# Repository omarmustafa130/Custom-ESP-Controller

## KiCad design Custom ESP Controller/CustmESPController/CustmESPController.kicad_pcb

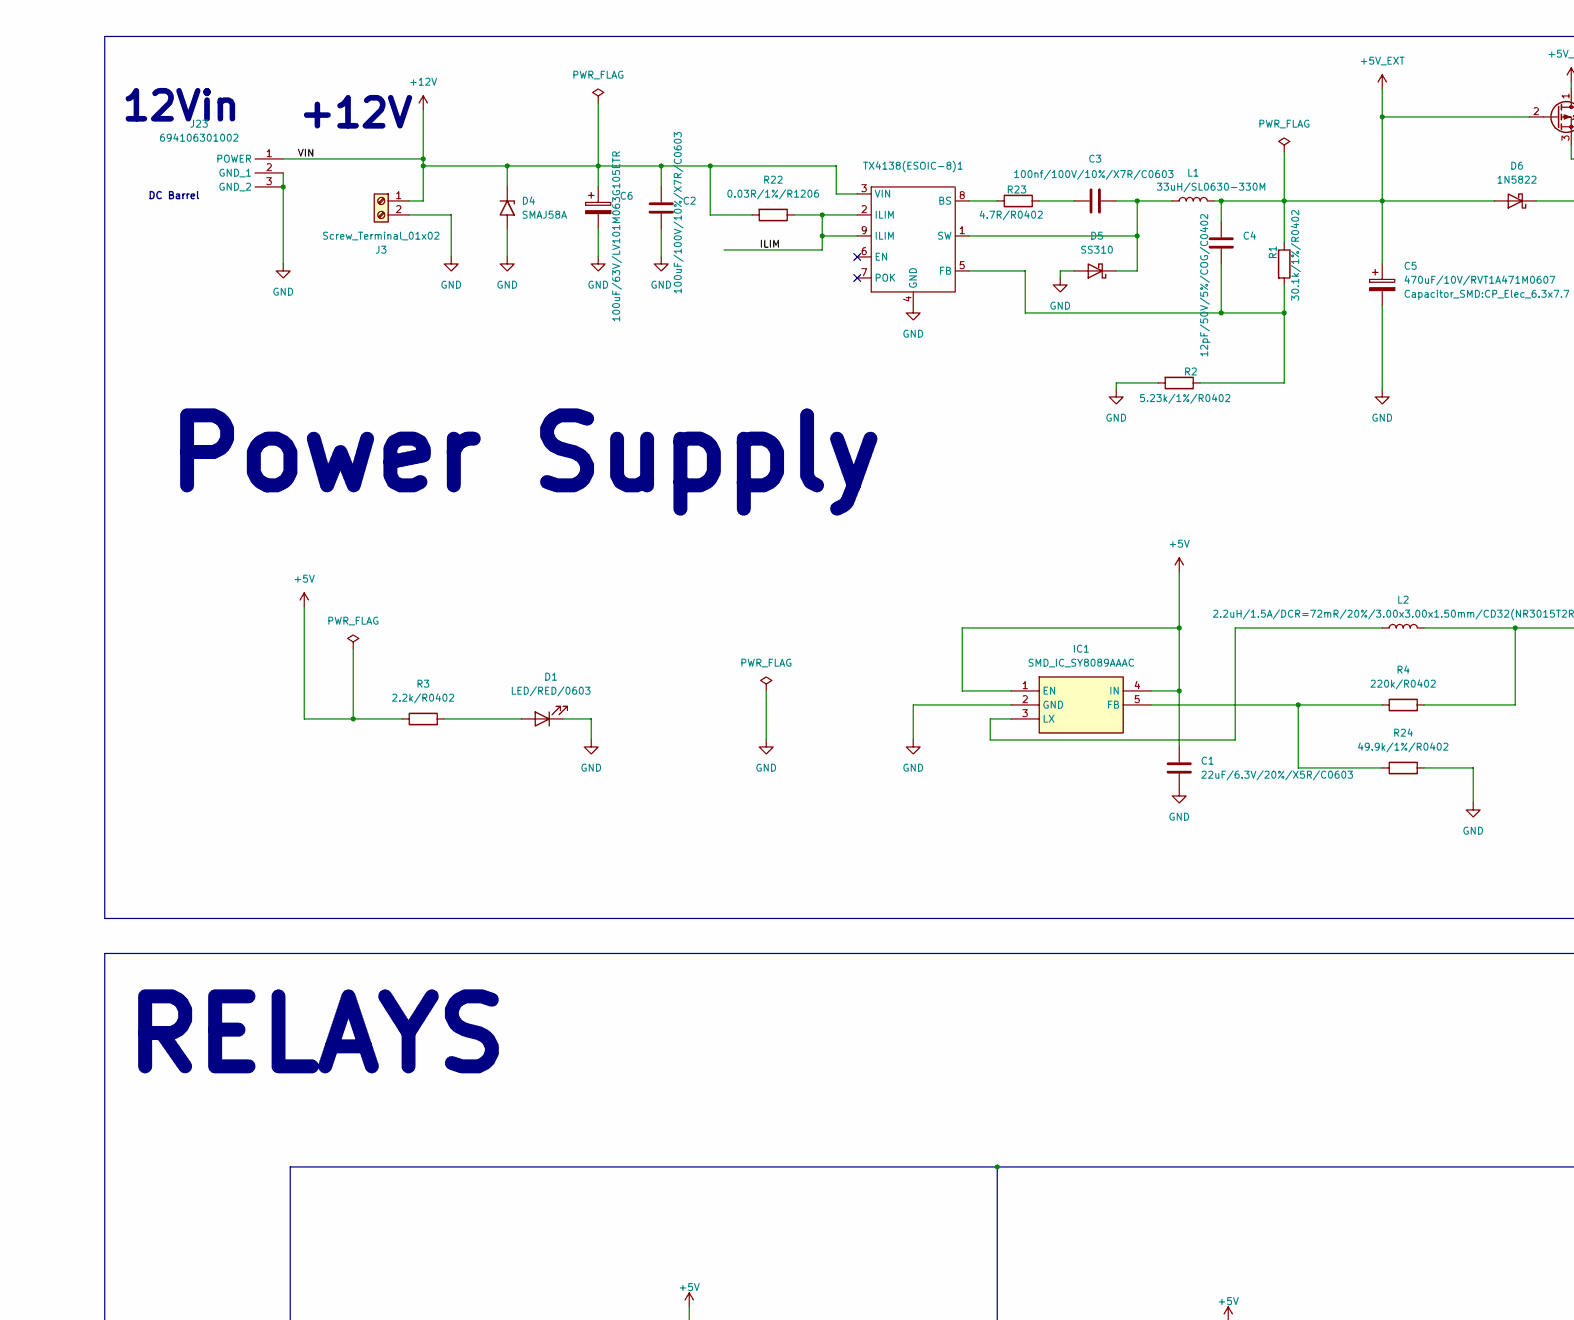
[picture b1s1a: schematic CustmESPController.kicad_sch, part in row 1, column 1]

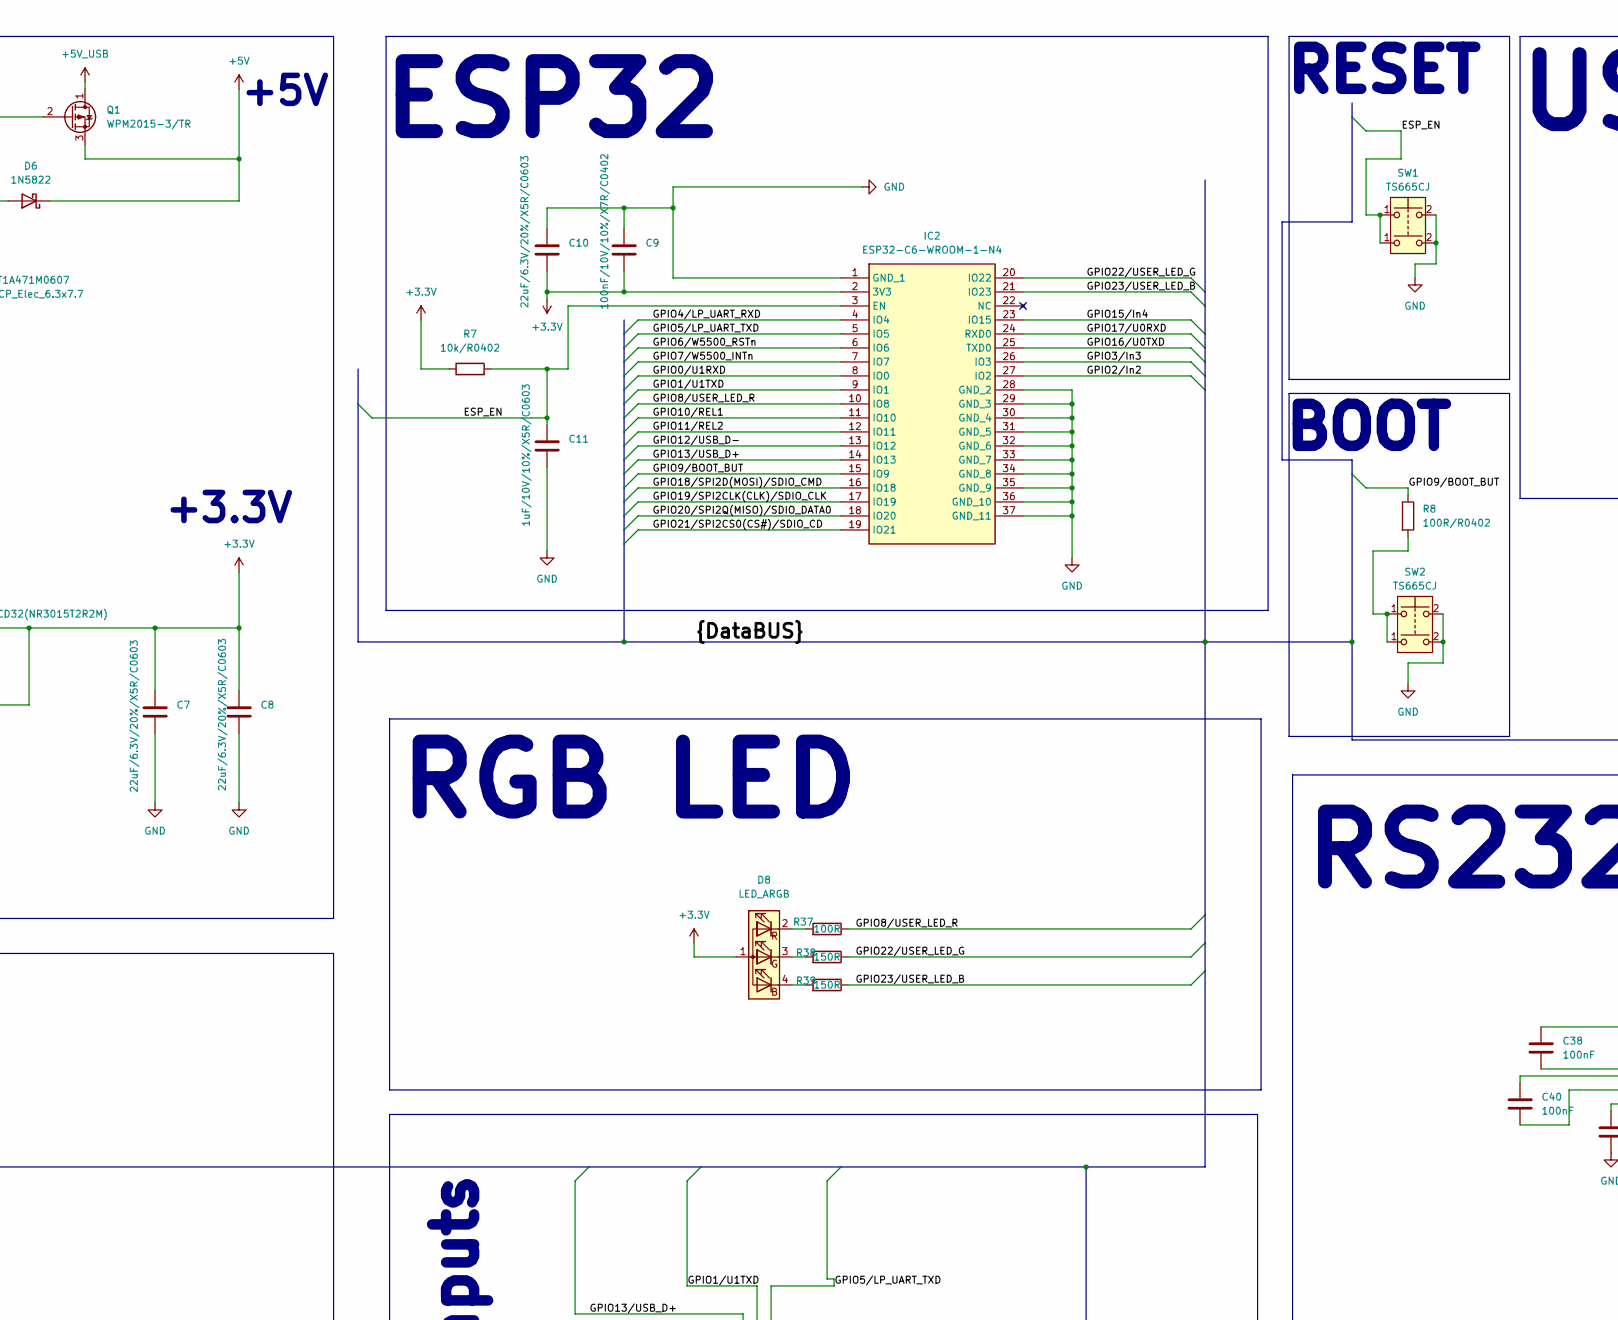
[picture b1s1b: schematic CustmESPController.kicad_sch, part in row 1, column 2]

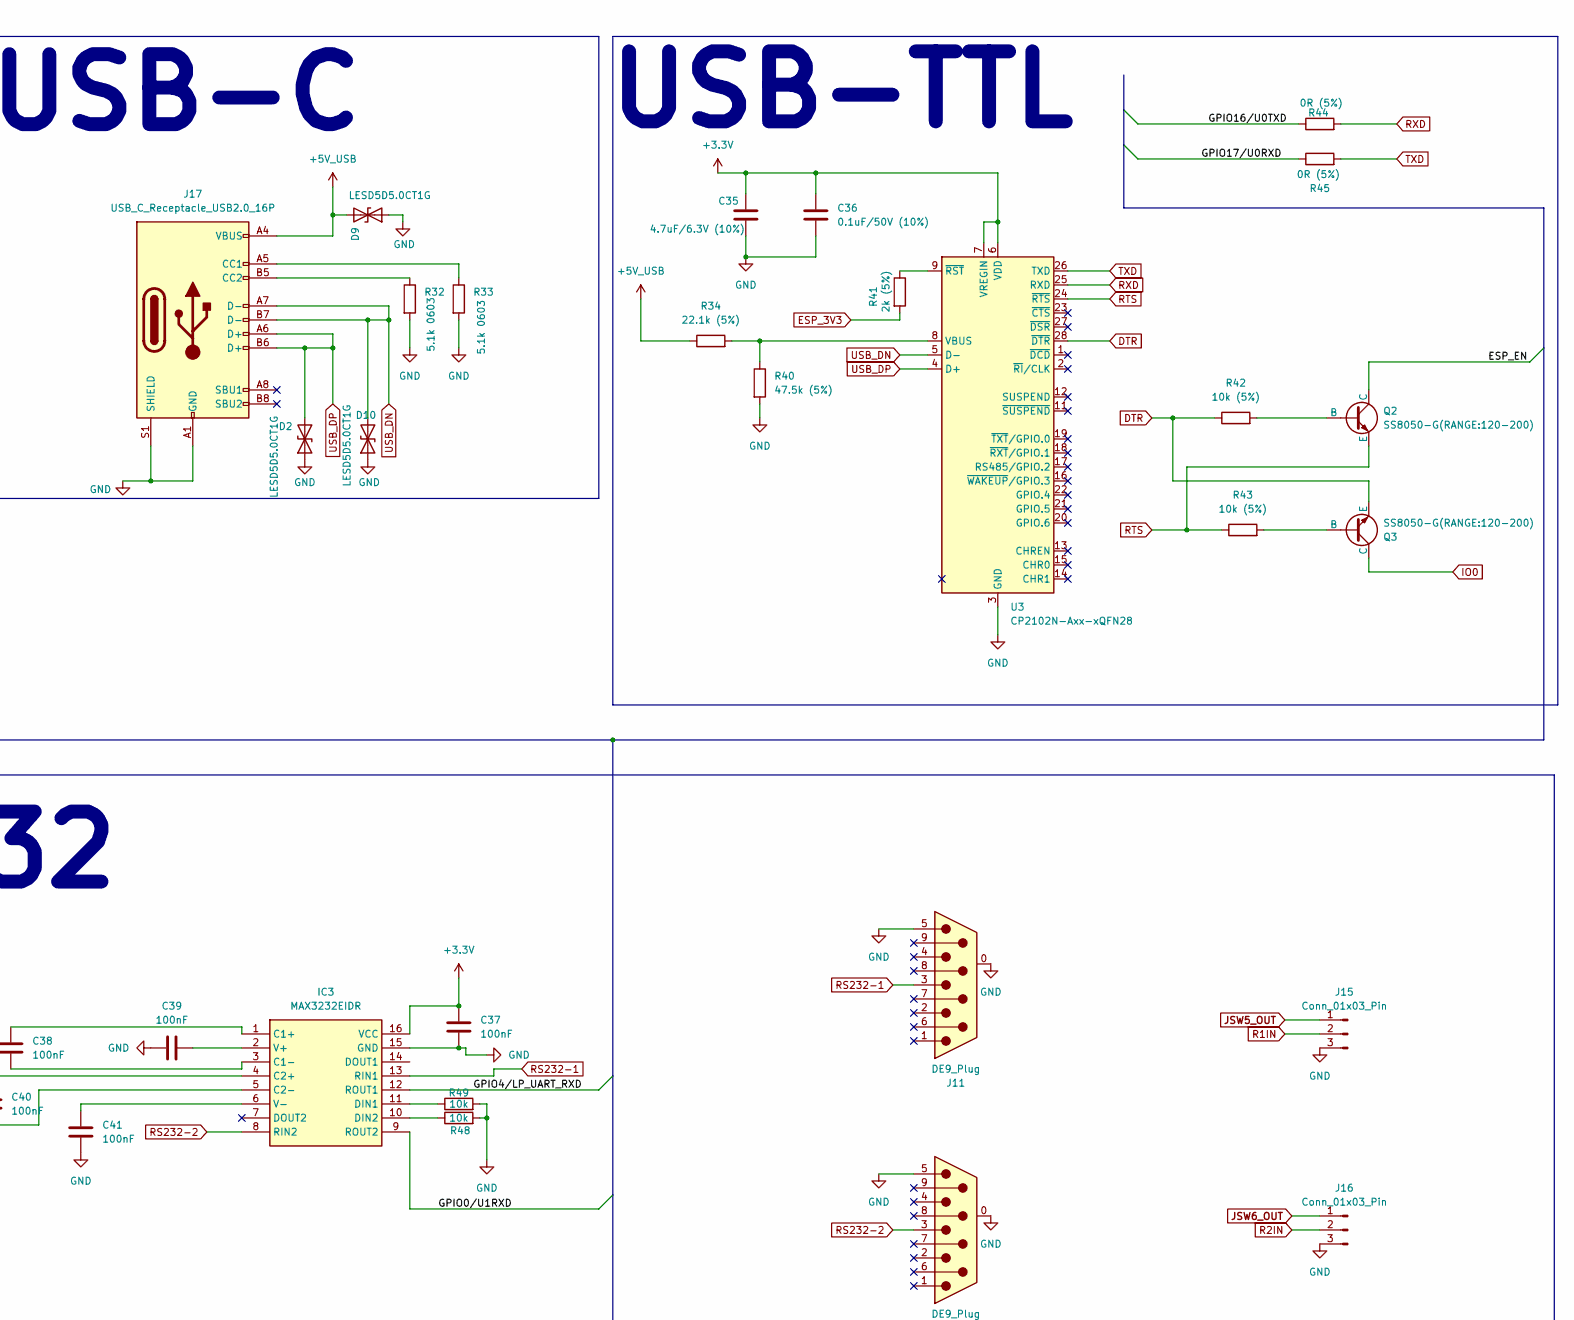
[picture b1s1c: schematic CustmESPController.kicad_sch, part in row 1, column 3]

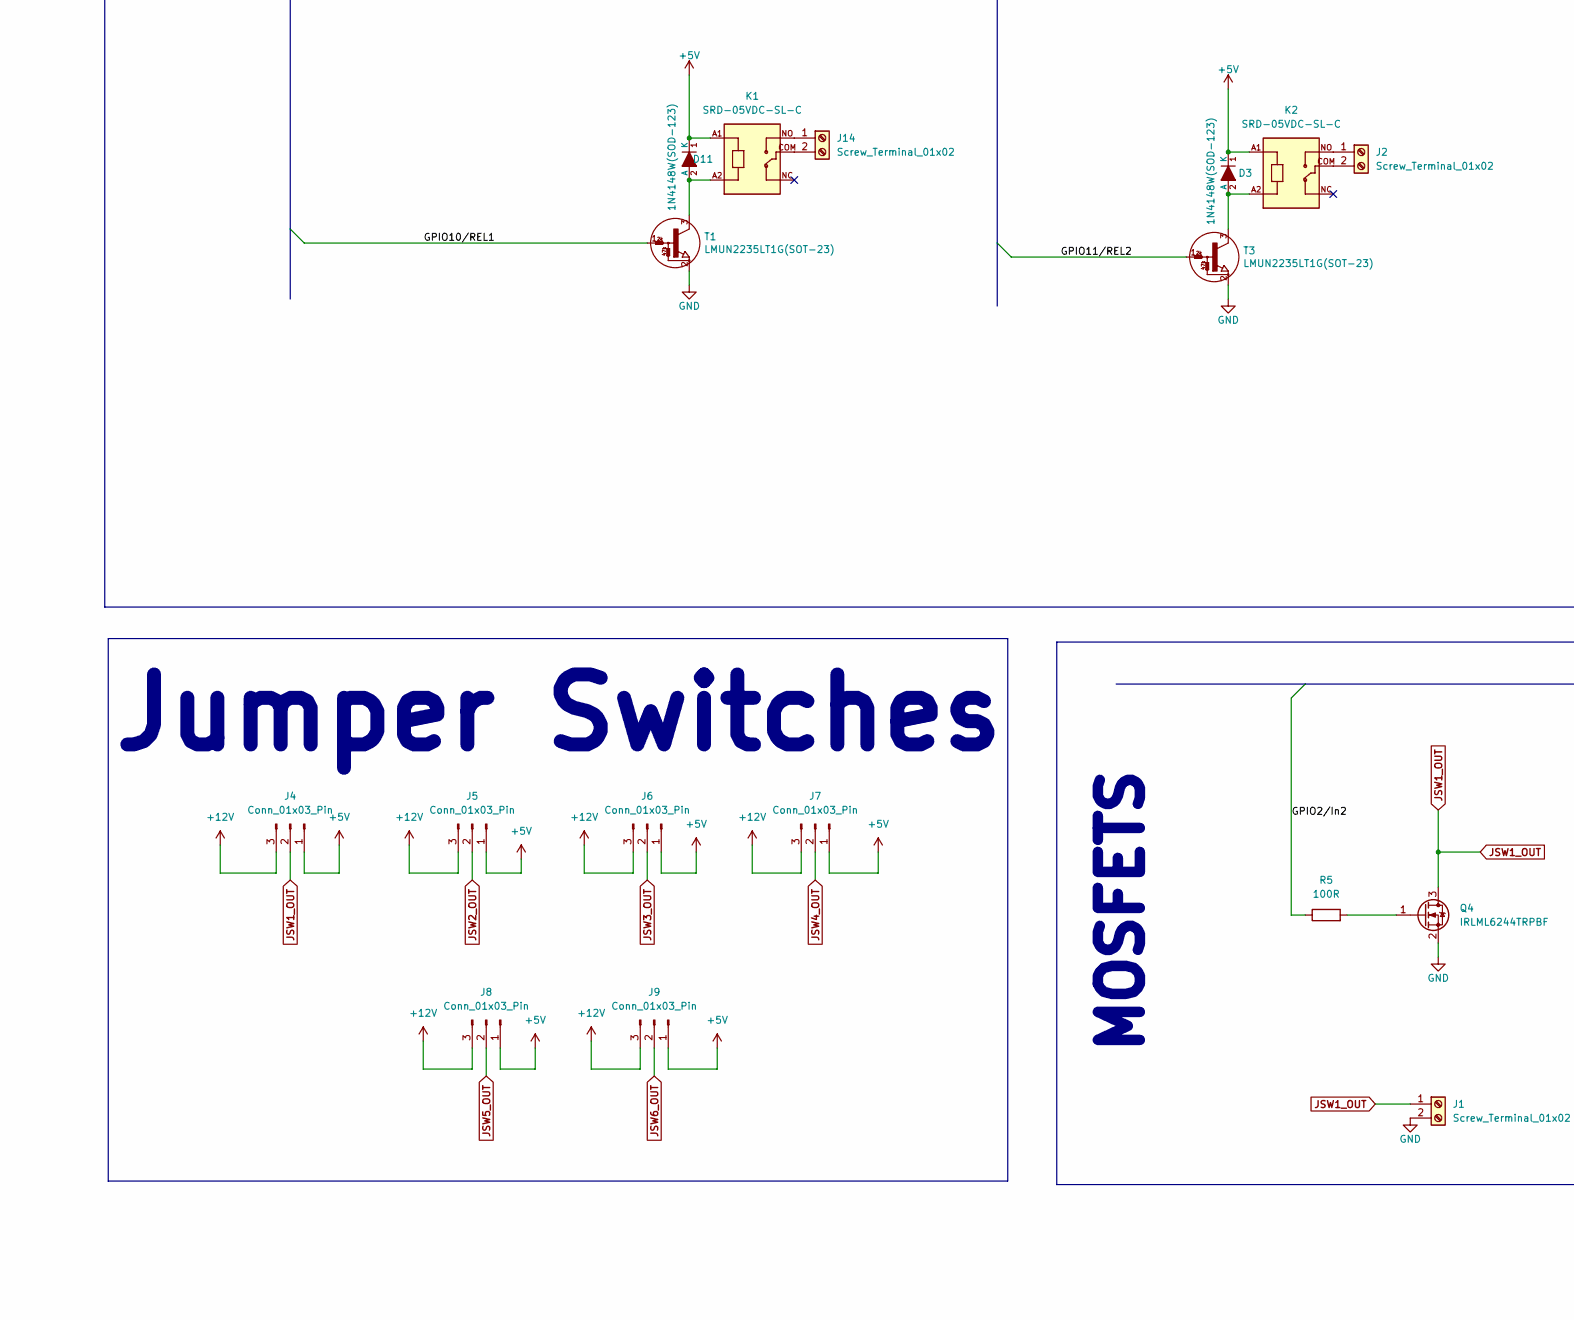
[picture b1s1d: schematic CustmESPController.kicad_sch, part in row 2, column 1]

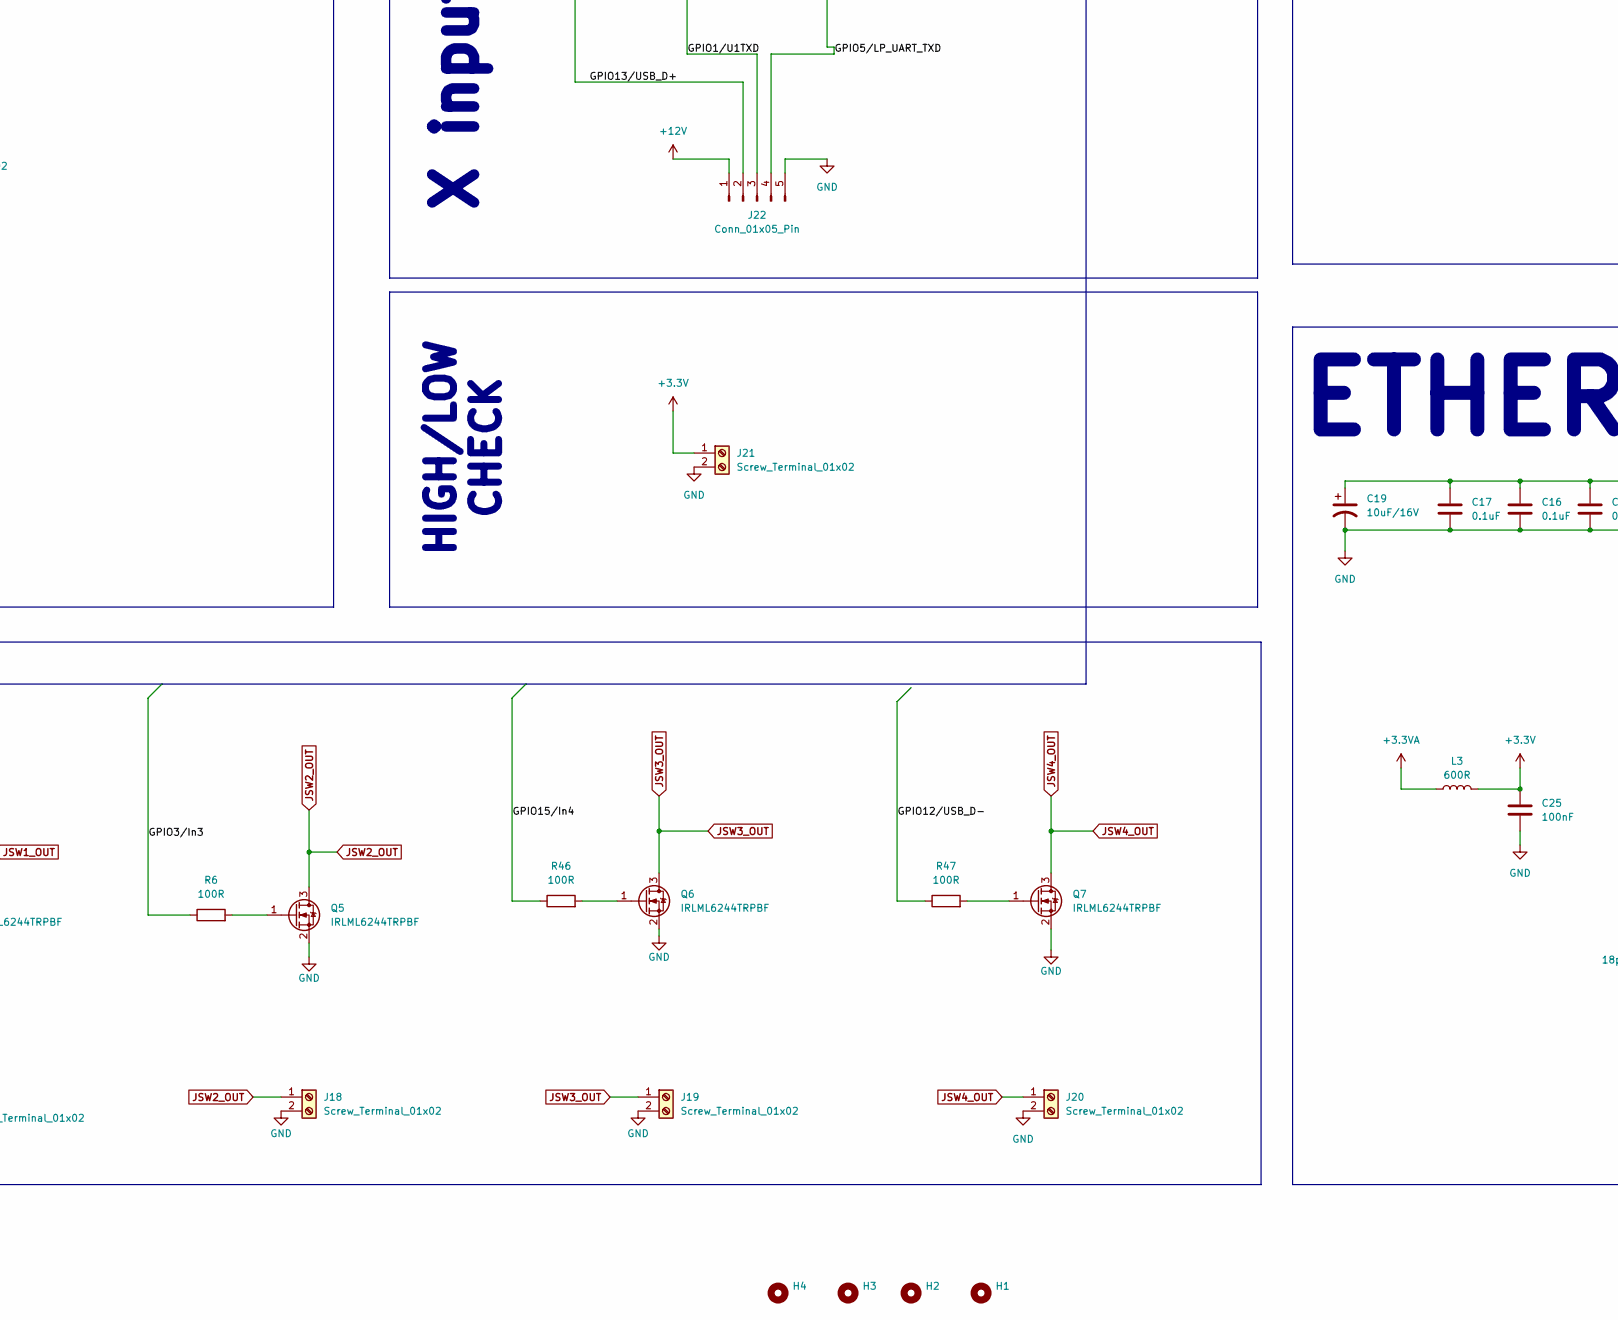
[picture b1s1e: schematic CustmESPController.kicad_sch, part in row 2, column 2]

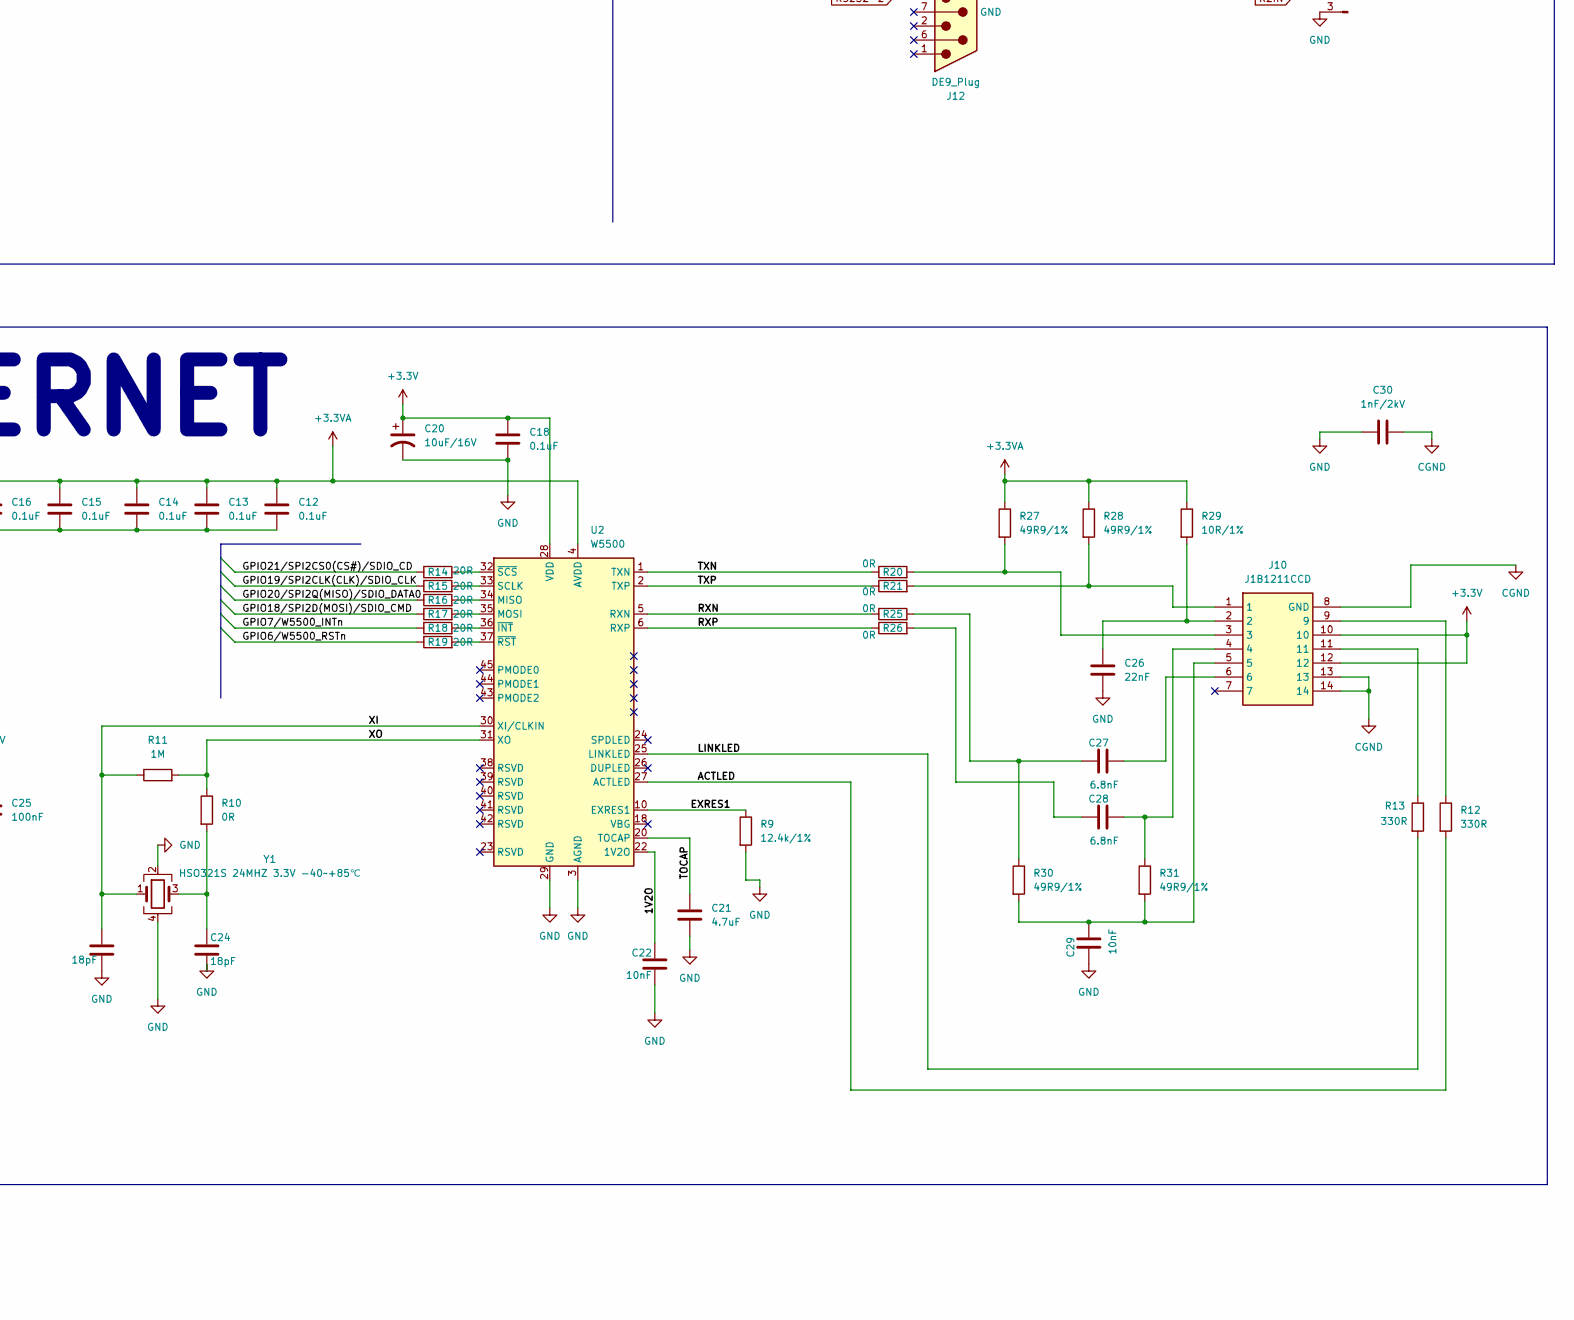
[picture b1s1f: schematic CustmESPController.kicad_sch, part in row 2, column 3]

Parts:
C1, C7, C8, C10: 22uF/6.3V/20%/X5R/C0603; C_0603_1608Metric
C2: 100uF/100V/10%/X7R/C0603; C_0603_1608Metric
C3: 100nf/100V/10%/X7R/C0603; C_0603_1608Metric
C4: 12pF/50V/5%/COG/C0402; C_0402_1005Metric
C5: 470uF/10V/RVT1A471M0607; CP_Elec_6.3x7.7
C6: 100uF/63V/LV101M063G105ETR; CP_Elec_10x10.5
C9: 100nF/10V/10%/X7R/C0402; C_0402_1005Metric
C11: 1uF/10V/10%/X5R/C0603; C_0603_1608Metric
C12, C13, C14, C15, C16, C17, C18: 0.1uF; C_0402_1005Metric
C19, C20: 10uF/16V; C_0603_1608Metric
C21: 4.7uF; C_0402_1005Metric
C22, C29: 10nF; C_0402_1005Metric
C23, C24: 18pF; C_0402_1005Metric
C25: 100nF; C_0402_1005Metric
C26: 22nF; C_0402_1005Metric
C27, C28: 6.8nF; C_0402_1005Metric
C30: 1nF/2kV; C_0402_1005Metric
C35: 4.7uF/6.3V (10%); C_0603_1608Metric
C36: 0.1uF/50V (10%); C_0603_1608Metric
C37, C38, C39, C40, C41: 100nF; C_0603_1608Metric
D1: LED/RED/0603; LED_0603_1608Metric
D2, D9, D10: LESD5D5.0CT1G; LESD5D5.0CT1G_DTVS
D3, D11: 1N4148W(SOD-123); 1N4148W_SODFL3816X120N
D4: SMAJ58A; SMAJ58A_DIOM5026X229N
D5: SS310; DIO_SS310
D6: 1N5822; 1N5822_DIOAD3070W130L950D530
D8: LED_ARGB; LED_D5.0mm-4_RGB
H1, H2, H3, H4: MountingHole_2.2mm_M2
IC1: SMD_IC_SY8089AAAC; SY80B9AAAC_SOT95P285X140-5N; Mouser Part Number 909-SMDICSY8089AAAC
IC2: ESP32-C6-WROOM-1-N4; ESP32C6WROOM1N4; Mouser Part Number 356-ESP32C6WROOM1N4
IC3: MAX3232EIDR; MAX3232EIDR_SOIC127P600X175-16N; Mouser Part Number 595-MAX3232EIDR
J1, J2, J3, J14, J18, J19, J20, J21: Screw_Terminal_01x02; TerminalBlock_Altech_AK300-2_P5.00mm
J4, J5, J6, J7, J8, J9: Conn_01x03_Pin; PinHeader_1x03_P2.54mm_Vertical
J10: J1B1211CCD; Mouser Part Number 950-J1B1211CCD
J11, J12: DE9_Plug; DSUB-9_Female_Vertical_P2.77x2.84mm_MountingHoles
J15, J16: Conn_01x03_Pin; JST_EH_B3B-EH-A_1x03_P2.50mm_Vertical
J17: USB_C_Receptacle_USB2.0_16P; USB_C_Receptacle_HRO_TYPE-C-31-M-12
J22: Conn_01x05_Pin; JST_EH_B5B-EH-A_1x05_P2.50mm_Vertical
J23: 694106301002; 694106301002_1; Mouser Part Number 710-694106301002
K1, K2: SRD-05VDC-SL-C; RELAY_SRD-05VDC-SL-C
L1: 33uH/SL0630-330M; SL0630-330M
L2: 2.2uH/1.5A/DCR=72mR/20%/3.00x3.00x1.50mm/CD32(NR3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; IND_NR3015T2R2M
L3: 600R; L_0603_1608Metric
Q1: WPM2015-3/TR; WPM2015-3TR_SOT95P240X130-3N
Q2, Q3: SS8050-G(RANGE:120-200); SS8050_SOT95P240X115-3N
Q4, Q5, Q6, Q7: IRLML6244TRPBF; IRLML6244TRPBF_SOT95P237X112-3N
R1: 30.1k/1%/R0402; R_0402_1005Metric
R2: 5.23k/1%/R0402; R_0402_1005Metric
R3: 2.2k/R0402; R_0402_1005Metric
R4: 220k/R0402; R_0402_1005Metric
R5, R6, R46, R47: 100R; R_0402_1005Metric
R7: 10k/R0402; R_0402_1005Metric
R8: 100R/R0402; R_0402_1005Metric
R9: 12.4k/1%; R_0402_1005Metric
R10, R20, R21, R25, R26: 0R; R_0402_1005Metric
R11: 1M; R_0402_1005Metric
R12, R13: 330R; R_0402_1005Metric
R14, R15, R16, R17, R18, R19: 20R; R_0402_1005Metric
R22: 0.03R/1%/R1206; R_1206_3216Metric
R23: 4.7R/R0402; R_0402_1005Metric
R24: 49.9k/1%/R0402; R_0402_1005Metric
R27, R28, R30, R31: 49R9/1%; R_0402_1005Metric
R29: 10R/1%; R_0402_1005Metric
R32, R33: 5.1k 0603; R_0603_1608Metric
R34: 22.1k (5%); R_0603_1608Metric
R37: 100R; R_0603_1608Metric
R38, R39: 150R; R_0603_1608Metric
R40: 47.5k (5%); R_0603_1608Metric
R41: 2k (5%); R_0603_1608Metric
R42, R43: 10k (5%); R_0603_1608Metric
R44, R45: 0R (5%); R_0603_1608Metric
R48, R49: 10k; R_0402_1005Metric
SW1, SW2: TS665CJ; SW_PUSH_6mm
T1, T3: LMUN2235LT1G(SOT-23); LMUN2235LT1G
TX4138(ESOIC-8)1: TX4138_SOIC127P600X165-9N
U2: W5500; W5500_QFP50P900X900X160-48N
U3: CP2102N-Axx-xQFN28; CP2102N_QFN50P500X500X80-29N-D
Y1: HSO321S 24MHZ 3.3V -40~+85℃; HSO321S

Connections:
+3.3V: C7.1, C8.1, C9.2, C10.2, C18.1, C20.1, C25.1, C35.2, C36.2, C37.1, D8.1 (A), IC2.2 (3V3), IC3.16 (VCC), J10.10, J10.12, J21.1, L2.2, L3.2, R4.2, R7.1, U2.28 (VDD), U3.6 (VDD), U3.7 (VREGIN)
+3.3VA: C12.1, C13.1, C14.1, C15.1, C16.1, C17.1, C19.1, L3.1, R27.1, R28.1, R29.1, U2.4 (AVDD), U2.8 (AVDD), U2.11 (AVDD), U2.15 (AVDD), U2.17 (AVDD), U2.21 (AVDD)
+5V: C1.1, D3.1 (K), D6.1 (K), D11.1 (K), IC1.1 (EN), IC1.4 (IN), J4.1, J5.1, J6.1, J7.1, J8.1, J9.1, K1.A1, K2.A1, Q1.3 (S), R3.1
+5V_EXT: C4.1, C5.1, D6.2 (A), L1.2, Q1.2 (G), R1.1
+5V_USB: D9.2 (A2), J17.A4 (VBUS), J17.A9 (VBUS), J17.B4 (VBUS), J17.B9 (VBUS), Q1.1 (D), R34.1
+12V: C2.1, C6.1, D4.1 (A1), J3.1, J4.3, J5.3, J6.3, J7.3, J8.3, J9.3, J22.1, J23.1 (POWER), R22.2, TX4138(ESOIC-8)1.3 (VIN); also elsewhere on the board
/1V2O: C22.1, U2.22 (1V2O)
/ACTLED: R12.2, U2.27 (ACTLED)
/ESP_EN: C11.1, IC2.3 (EN), Q2.1 (C), R7.2, SW1.1
/EXRES1: R9.1, U2.10 (EXRES1)
/GPIO0/U1RXD: IC2.8 (IO0), IC3.9 (ROUT2)
/GPIO1/U1TXD: IC2.9 (IO1), J22.3
/GPIO2/In2: IC2.27 (IO2), R5.1
/GPIO3/In3: IC2.26 (IO3), R6.1
/GPIO4/LP_UART_RXD: IC2.4 (IO4), IC3.12 (ROUT1)
/GPIO5/LP_UART_TXD: IC2.5 (IO5), J22.4
/GPIO6/W5500_RSTn: IC2.6 (IO6), R19.1
/GPIO7/W5500_INTn: IC2.7 (IO7), R18.1
/GPIO8/USER_LED_R: IC2.10 (IO8), R37.1
/GPIO9/BOOT_BUT: IC2.15 (IO9), R8.1
/GPIO10/REL1: IC2.11 (IO10), T1.1 (B)
/GPIO11/REL2: IC2.12 (IO11), T3.1 (B)
/GPIO12/USB_D-: IC2.13 (IO12), R47.1
/GPIO13/USB_D+: IC2.14 (IO13), J22.2
/GPIO15/In4: IC2.23 (IO15), R46.1
/GPIO16/U0TXD: IC2.25 (TXD0), R44.1
/GPIO17/U0RXD: IC2.24 (RXD0), R45.1
/GPIO18/SPI2D(MOSI)/SDIO_CMD: IC2.16 (IO18), R17.1
/GPIO19/SPI2CLK(CLK)/SDIO_CLK: IC2.17 (IO19), R15.1
/GPIO20/SPI2Q(MISO)/SDIO_DATA0: IC2.18 (IO20), R16.1
/GPIO21/SPI2CS0(CS#)/SDIO_CD: IC2.19 (IO21), R14.1
/GPIO22/USER_LED_G: IC2.20 (IO22), R38.1
/GPIO23/USER_LED_B: IC2.21 (IO23), R39.1
/ILIM: R22.1, TX4138(ESOIC-8)1.2 (ILIM), TX4138(ESOIC-8)1.9 (ILIM); also elsewhere on the board
/LINKLED: R13.2, U2.25 (LINKLED)
/RXN: R25.1, U2.5 (RXN)
/RXP: R26.1, U2.6 (RXP)
/TOCAP: C21.1, U2.20 (TOCAP)
/TXN: R20.1, U2.1 (TXN)
/TXP: R21.1, U2.2 (TXP)
/XI: C23.1, R11.1, U2.30 (XI/CLKIN), Y1.1
/XO: R10.1, R11.2, U2.31 (XO)
CGND: C30.2, J10.8 (GND), J10.13, J10.14
DTR: Q3.3 (E), R42.1, U3.28 (~DTR)
ESP_3V3: R41.2
GND: C1.2, C2.2, C5.2, C6.2, C7.2, C8.2, C9.1, C10.1, C11.2, C12.2, C13.2, C14.2, C15.2, C16.2, C17.2, C18.2, C19.2, C20.2, C21.2, C22.2, C23.2, C24.2, C25.2, C26.2, C29.1, C30.1, C35.1, C36.1, C37.2, C39.1, C41.2, D1.1 (K), D2.1 (A1), D4.2 (A2), D5.2 (A), D9.1 (A1), D10.1 (A1), IC1.2 (GND), IC2.1 (GND_1), IC2.28 (GND_2), IC2.29 (GND_3), IC2.30 (GND_4), IC2.31 (GND_5), IC2.32 (GND_6), IC2.33 (GND_7), IC2.34 (GND_8), IC2.35 (GND_9), IC2.36 (GND_10), IC2.37 (GND_11), IC3.15 (GND), J1.2, J3.2, J11.0 (GND), J11.5, J12.0 (GND), J12.5, J15.3, J16.3, J17.A1 (GND), J17.A12 (GND), J17.B1 (GND), J17.B12 (GND), J17.S1 (SHIELD), J18.2, J19.2, J20.2, J21.2, J22.5, J23.2 (GND_1), J23.3 (GND_2), Q4.2 (S), Q5.2 (S), Q6.2 (S), Q7.2 (S), R2.2, R9.2, R24.2, R32.2, R33.2, R40.2, R48.2, R49.2, SW1.2, SW2.2, T1.2 (E), T3.2 (E), TX4138(ESOIC-8)1.4 (GND), U2.3 (AGND), U2.9 (AGND), U2.14 (AGND), U2.16 (AGND), U2.19 (AGND), U2.29 (GND), U2.48 (AGND), U3.3 (GND), U3.29 (GND), Y1.2, Y1.4; also elsewhere on the board
IO0: Q3.1 (C)
JSW1_OUT: J1.1, J4.2, Q4.3 (D)
JSW2_OUT: J5.2, J18.1, Q5.3 (D)
JSW3_OUT: J6.2, J19.1, Q6.3 (D)
JSW4_OUT: J7.2, J20.1, Q7.3 (D)
JSW5_OUT: J8.2, J15.1
JSW6_OUT: J9.2, J16.1
unnamed: C3.1, R23.2
unnamed: C24.1, R10.2, Y1.3
unnamed: C26.1, J10.2, R29.2
unnamed: C27.1, R25.2, R30.1
unnamed: C27.2, J10.6
unnamed: C28.1, R26.2
unnamed: C28.2, J10.4, R31.1
unnamed: C29.2, J10.5, R30.2, R31.2
unnamed: D1.2 (A), R3.2
unnamed: D3.2 (A), K2.A2, T3.3 (C)
unnamed 63: C3.2, D5.1 (K), L1.1, TX4138(ESOIC-8)1.1 (SW); also elsewhere on the board
unnamed: D8.4 (BK), R39.2
unnamed: D8.3 (GK), R38.2
unnamed: D8.2 (RK), R37.2
unnamed: D11.2 (A), K1.A2, T1.3 (C)
unnamed: IC1.5 (FB), R4.1, R24.1
unnamed: IC1.3 (LX), L2.1
unnamed: C38.1, IC3.1 (C1+)
unnamed: C38.2, IC3.3 (C1-)
unnamed: C40.1, IC3.4 (C2+)
unnamed: C40.2, IC3.5 (C2-)
unnamed: IC3.11 (DIN1), R49.1
unnamed: IC3.10 (DIN2), R48.1
unnamed: C39.2, IC3.2 (V+)
unnamed: C41.1, IC3.6 (V-)
unnamed: J2.1, K2.NO
unnamed: J2.2, K2.COM
unnamed: J10.1, R21.2, R28.2
unnamed: J10.3, R20.2, R27.2
unnamed: J10.9, R12.1
unnamed: J10.11, R13.1
unnamed: J14.1, K1.NO
unnamed: J14.2, K1.COM
unnamed: J17.A5 (CC1), R33.1
unnamed: J17.B5 (CC2), R32.1
unnamed: Q2.2 (B), R42.2
unnamed: Q3.2 (B), R43.2
unnamed: Q4.1 (G), R5.2
unnamed: Q5.1 (G), R6.2
unnamed: Q6.1 (G), R46.2
unnamed: Q7.1 (G), R47.2
unnamed: R8.2, SW2.1
unnamed 95: R23.1, TX4138(ESOIC-8)1.8 (BS); also elsewhere on the board
unnamed 96: C4.2, R1.2, R2.1, TX4138(ESOIC-8)1.5 (FB); also elsewhere on the board
unnamed: R16.2, U2.34 (MISO)
unnamed: R17.2, U2.35 (MOSI)
unnamed: R15.2, U2.33 (SCLK)
unnamed: R18.2, U2.36 (~INT)
unnamed: R19.2, U2.37 (~RST)
unnamed: R14.2, U2.32 (~SCS)
unnamed: R34.2, R40.1, U3.8 (VBUS)
unnamed: R41.1, U3.9 (~RST)
R1IN: J15.2
R2IN: J16.2
RS232-1: IC3.13 (RIN1), J11.3
RS232-2: IC3.8 (RIN2), J12.3
RTS: Q2.3 (E), R43.1, U3.24 (~RTS)
RXD: R44.2, U3.25 (RXD)
TXD: R45.2, U3.26 (TXD)
USB_DN: D10.2 (A2), J17.A7 (D-), J17.B7 (D-), U3.5 (D-)
USB_DP: D2.2 (A2), J17.A6 (D+), J17.B6 (D+), U3.4 (D+)

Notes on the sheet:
BOOT
12Vin
USB-C
ETHERNET
+5V
Jumper Switches
HIGH/LOW CHECK
RESET
X inputs
USB-TTL
Power Supply
DC Barrel
RELAYS
+3.3V
MOSFETS
RS232
+12V
RGB LED
ESP32

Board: 2 copper layers, 143 parts (0 on the bottom side), 110 nets, no tracks yet.

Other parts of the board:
TX4138: TX4138_SOIC127P600X165-9N

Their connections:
+12V: TX4138.3 (VIN); also elsewhere on the board
/ILIM: TX4138.2 (ILIM), TX4138.9 (ILIM); also elsewhere on the board
GND: TX4138.4 (GND); also elsewhere on the board
unnamed 63: TX4138.1 (SW); also elsewhere on the board
unnamed 95: TX4138.8 (BS); also elsewhere on the board
unnamed 96: TX4138.5 (FB); also elsewhere on the board

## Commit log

2025-05-18 Schematics done
2025-05-19 3D PCB done
2025-05-22 3D PCB
